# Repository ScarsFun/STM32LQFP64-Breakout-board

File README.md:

# STM32 LQFP64 BREAKOUT BOARD

This is a 64pin STM32 BREAKOUT BOARD inspired by "blue pill" STM32 48pin board (Maple mini clone).
Same features are Improved:

* 3.3v Power supply and VDDA improvements. 
* USB ESD protection.
* added USB reset circuit (not needed for some MCUs).
* Many Cortex M0, M3, M4 STM32 Microcontrolles may be mounted in this PCB layout.
Check notes in schematic and read STM32 datasheets. 
* Eagle PCB, Schematics.

* RTC oscillator is not implemented because no enought PCB spaces to follow STM design guide. ...I'll be pleased if anyone will find a solution 

# CHANGELOG
## 1.3.1 (2021-07-11)
### Fix:
- Fixed reset circuit.
- Silkscreen improvements.

## 1.3 (2020-06-16)
### Features:
- Added support for STM32F401, STM32F410, STM32F411, STM32F412, STM32F413, STM32F423, STM32F446
### Fix:
- Added partitor to VBUS  

## 1.2 (2018-10-11)
### Fix:
- RTC oscillator design dont works. removed from project 

## 1.1 (2018-07-23)
### Features:
- First release lot of bugs

This work is licensed under a [Creative Commons Attribution 4.0 International License.](http://creativecommons.org/licenses/by/4.0/)

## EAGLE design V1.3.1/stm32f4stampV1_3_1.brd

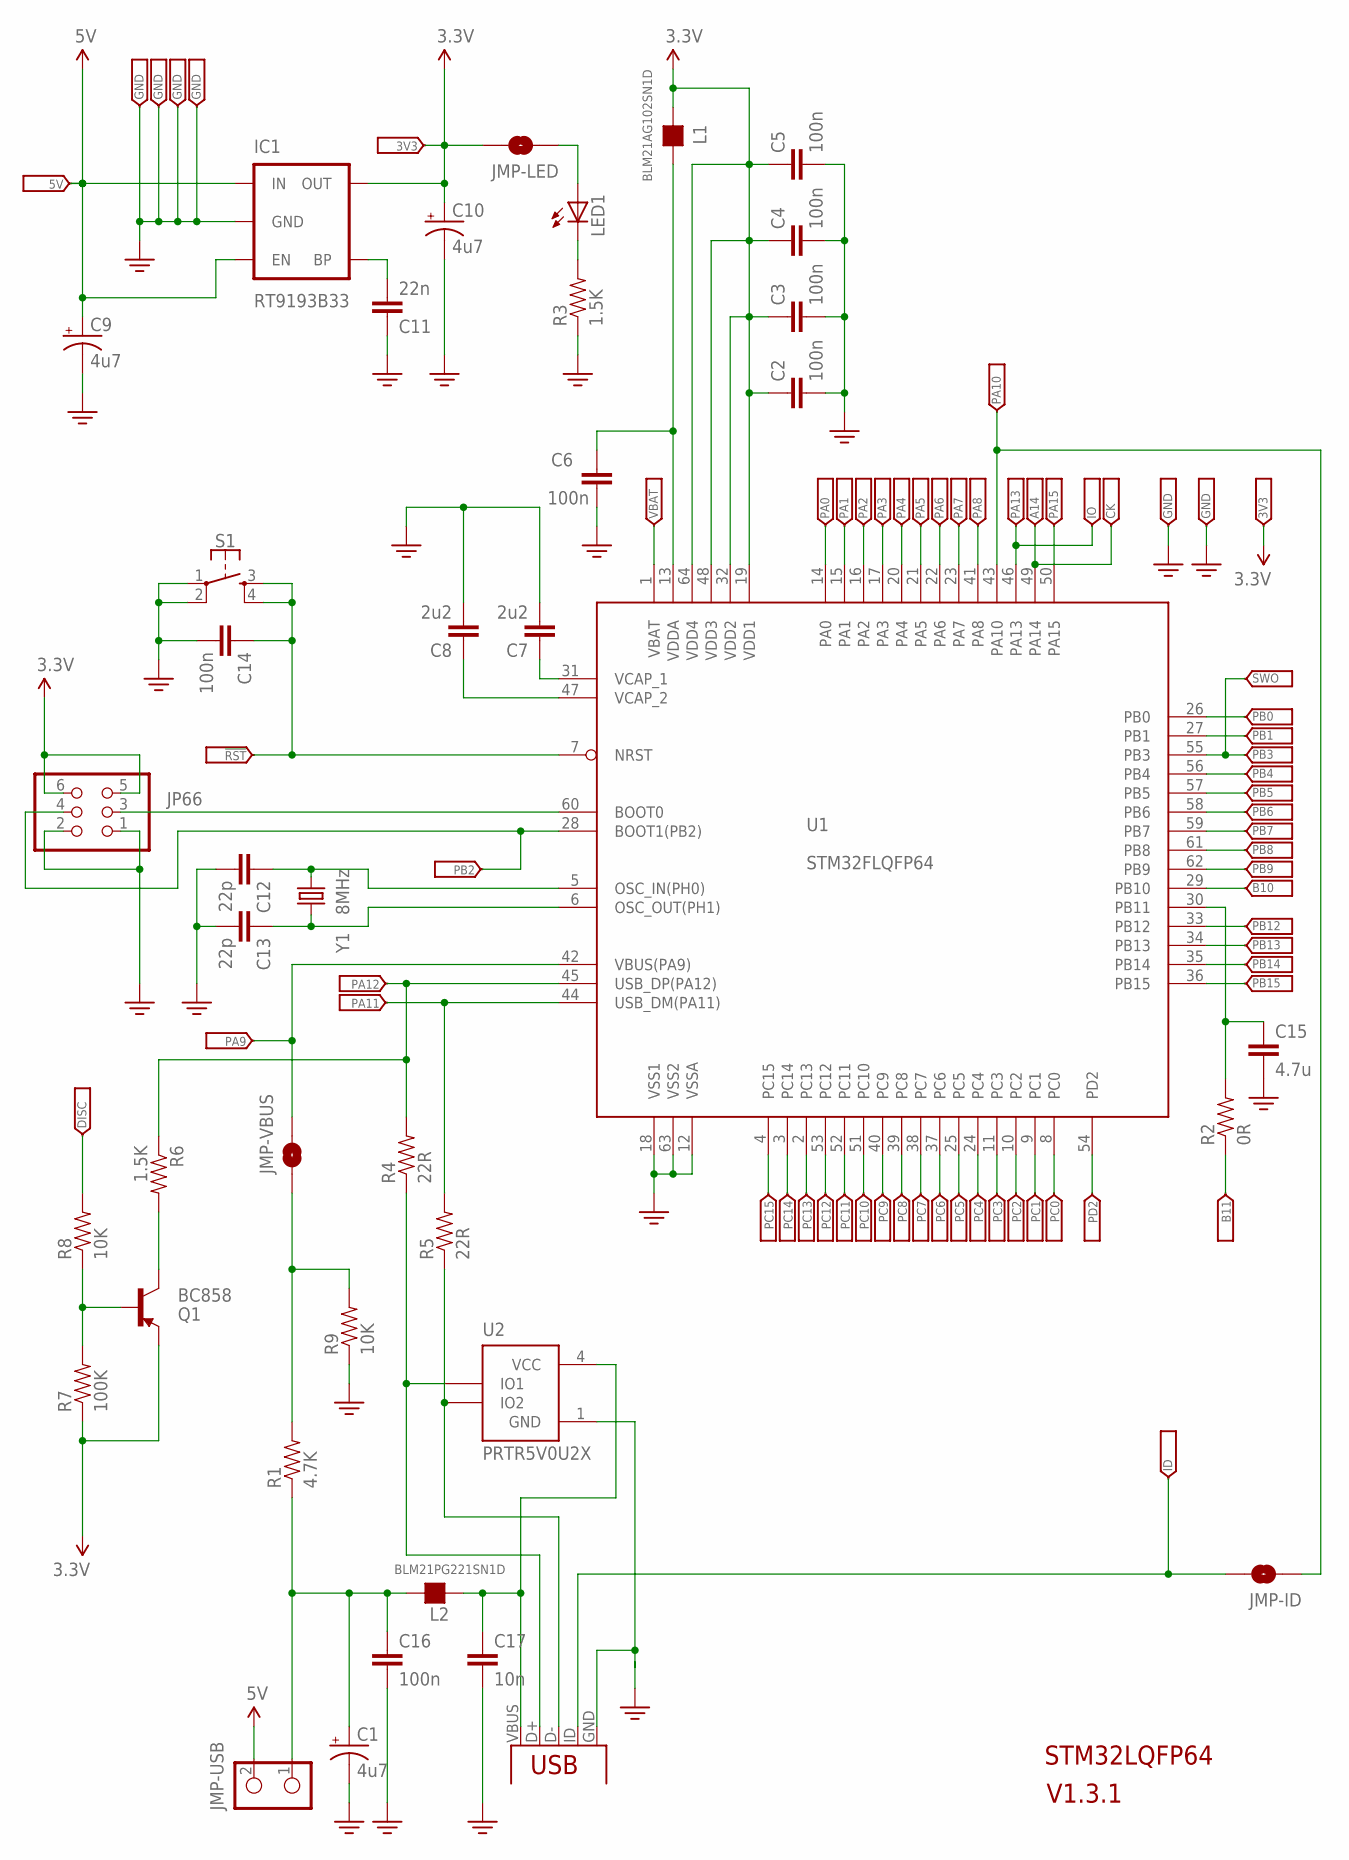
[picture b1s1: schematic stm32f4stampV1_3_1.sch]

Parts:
C1, C9, C10: 4u7; EIA3216-KIT
C2, C3, C4, C5, C6, C14, C16: 100n; 0805
C7, C8: 2u2; 0805
C11: 22n; 0805
C12, C13: 22p; 0805
C15: 4.7u; 0805
C17: 10n; 0805
IC1: RT9193B33; SOT23-5
JMP-ID: SOLDERJUMPERNO; SJ_2S-NO
JMP-LED: SOLDERJUMPERNO; SJ_2S-NO
JMP-USB: JUMPER-2PTH; 1X02
JMP-VBUS: SOLDERJUMPERNO; SJ_2S-NO
JP1: PA12; 1X1-HEADER-HOLE
JP2: 5V; 1X1-HEADER-HOLE
JP3, JP6, JP7, JP55, JP62, JP65: GND; 1X1-HEADER-HOLE
JP4, JP63: 3V3; 1X1-HEADER-HOLE
JP5: DISC; 1X1-HEADER-HOLE
JP8: PB8; 1X1-HEADER-HOLE
JP9: PA10; 1X1-HEADER-HOLE
JP10: PA8; 1X1-HEADER-HOLE
JP11: PA13; 1X1-HEADER-HOLE
JP12: PC9; 1X1-HEADER-HOLE
JP13: PC15; 1X1-HEADER-HOLE
JP14: PC14; 1X1-HEADER-HOLE
JP15: PC13; 1X1-HEADER-HOLE
JP16: PC12; 1X1-HEADER-HOLE
JP17: PC11; 1X1-HEADER-HOLE
JP18: PC10; 1X1-HEADER-HOLE
JP19: PC8; 1X1-HEADER-HOLE
JP20: PC7; 1X1-HEADER-HOLE
JP21: PC6; 1X1-HEADER-HOLE
JP22: PC5; 1X1-HEADER-HOLE
JP23: PC4; 1X1-HEADER-HOLE
JP24: PC3; 1X1-HEADER-HOLE
JP25: PC2; 1X1-HEADER-HOLE
JP26: PC1; 1X1-HEADER-HOLE
JP27: PC0; 1X1-HEADER-HOLE
JP28: PD2; 1X1-HEADER-HOLE
JP29: PA0; 1X1-HEADER-HOLE
JP30: PA1; 1X1-HEADER-HOLE
JP31: PA2; 1X1-HEADER-HOLE
JP32: PA3; 1X1-HEADER-HOLE
JP33: PA4; 1X1-HEADER-HOLE
JP34: PA5; 1X1-HEADER-HOLE
JP35: PA6; 1X1-HEADER-HOLE
JP36: PA7; 1X1-HEADER-HOLE
JP37: A14; 1X1-HEADER-HOLE
JP38: PA15; 1X1-HEADER-HOLE
JP39: PB0; 1X1-HEADER-HOLE
JP40: PB1; 1X1-HEADER-HOLE
JP41: PB3; 1X1-HEADER-HOLE
JP42: PB4; 1X1-HEADER-HOLE
JP43: PB5; 1X1-HEADER-HOLE
JP44: PB6; 1X1-HEADER-HOLE
JP45: PB7; 1X1-HEADER-HOLE
JP46: PB9; 1X1-HEADER-HOLE
JP47: B10; 1X1-HEADER-HOLE
JP48: B11; 1X1-HEADER-HOLE
JP49: PB12; 1X1-HEADER-HOLE
JP50: PB13; 1X1-HEADER-HOLE
JP51: PB14; 1X1-HEADER-HOLE
JP52: PB15; 1X1-HEADER-HOLE
JP53: VBAT; 1X1-HEADER-HOLE
JP54: !RST; 1X1-HEADER-HOLE
JP56: ID; 1X1-HEADER-HOLE
JP57: PB2; 1X1-HEADER-HOLE
JP58: PA11; 1X1-HEADER-HOLE
JP59: IO; 1X1-HEADER-HOLE
JP60: CK; 1X1-HEADER-HOLE
JP61: SWO; 1X1-HEADER-HOLE
JP64: PA9; 1X1-HEADER-HOLE
JP66: PINHD-2X3; 2X03
L1: BLM21AG102SN1D; L0805
L2: BLM21PG221SN1D; L0805
LED1: LEDSML0805; SML0805
Q1: BC858; SOT23-3
R1: 4.7K; 0805
R2: 0R; 0805
R3, R6: 1.5K; 0805
R4, R5: 22R; 0805
R7: 100K; 0805
R8, R9: 10K; 0805
S1: MOMENTARY-SWITCH-SPST-2-SMD-5.2MM; TACTILE_SWITCH_SMD_5.2MM
U1: STM32FLQFP64; LQFP64
U2: PRTR5V0U2X; SOT-143B
USB: USB-MICROB-SMD
Y1: 8MHz; CRYSTAL-SMD-5X3

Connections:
3.3V: C2.1, C3.1, C4.1, C5.1, C10.A (+), IC1.5 (OUT), JMP-LED.2, JP4.1, JP63.1, JP66.5, JP66.6, L1.2, Q1.2 (E), R7.1, U1.19 (VDD1), U1.32 (VDD2), U1.48 (VDD3), U1.64 (VDD4)
5V: C9.A (+), IC1.1 (IN), IC1.3 (EN), JMP-USB.2, JP2.1
GND: C1.C (-), C2.2, C3.2, C4.2, C5.2, C6.2, C7.2, C8.2, C9.C (-), C10.C (-), C11.1, C12.2, C13.2, C14.2, C15.2, C16.2, C17.2, IC1.2 (GND), JP3.1, JP6.1, JP7.1, JP55.1, JP62.1, JP65.1, JP66.1, JP66.2, R3.1, R9.1, S1.1, S1.2, U1.12 (VSSA), U1.18 (VSS1), U1.63 (VSS2), U2.1 (GND), USB.GND, USB.MT1, USB.MT2, USB.MT3, USB.MT4
unnamed: JP1.1, R4.2, R6.1, U1.45 (USB_DP(PA12))
unnamed: JP13.1, U1.4 (PC15)
unnamed: C1.A (+), C16.1, JMP-USB.1, L2.2, R1.1
unnamed: JP12.1, U1.40 (PC9)
unnamed: C17.1, L2.1, U2.4 (VCC), USB.VBUS
unnamed: JP58.1, R5.2, U1.44 (USB_DM(PA11))
unnamed: JP8.1, U1.61 (PB8)
unnamed: C11.2, IC1.4 (BP)
unnamed: JP66.3, U1.60 (BOOT0)
unnamed: JP10.1, U1.41 (PA8)
unnamed: JP11.1, JP59.1, U1.46 (PA13)
unnamed: C13.1, U1.6 (OSC_OUT(PH1)), Y1.1
unnamed: C7.1, U1.31 (VCAP_1)
unnamed: C8.1, U1.47 (VCAP_2)
unnamed: C12.1, U1.5 (OSC_IN(PH0)), Y1.3 (2)
unnamed: JP57.1, JP66.4, U1.28 (BOOT1(PB2))
unnamed: C14.1, JP54.1, S1.3, S1.4, U1.7 (NRST)
unnamed: LED1.C, R3.2
unnamed: C6.1, L1.1, U1.13 (VDDA)
unnamed: JMP-ID.2, JP56.1, USB.ID
unnamed: R5.1, U2.3 (IO2), USB.D-
unnamed: JMP-ID.1, JP9.1, U1.43 (PA10)
unnamed: JP14.1, U1.3 (PC14)
unnamed: JMP-VBUS.1, R1.2, R9.2
unnamed: JP15.1, U1.2 (PC13)
unnamed: JP16.1, U1.53 (PC12)
unnamed: JP17.1, U1.52 (PC11)
unnamed: JP18.1, U1.51 (PC10)
unnamed: JP19.1, U1.39 (PC8)
unnamed: JP20.1, U1.38 (PC7)
unnamed: JP21.1, U1.37 (PC6)
unnamed: JP22.1, U1.25 (PC5)
unnamed: JP23.1, U1.24 (PC4)
unnamed: JP24.1, U1.11 (PC3)
unnamed: JP25.1, U1.10 (PC2)
unnamed: JP26.1, U1.9 (PC1)
unnamed: JP27.1, U1.8 (PC0)
unnamed: JP28.1, U1.54 (PD2)
unnamed: JP29.1, U1.14 (PA0)
unnamed: JP30.1, U1.15 (PA1)
unnamed: JP31.1, U1.16 (PA2)
unnamed: JP32.1, U1.17 (PA3)
unnamed: JP33.1, U1.20 (PA4)
unnamed: JP34.1, U1.21 (PA5)
unnamed: JP35.1, U1.22 (PA6)
unnamed: JP36.1, U1.23 (PA7)
unnamed: JP37.1, JP60.1, U1.49 (PA14)
unnamed: JP38.1, U1.50 (PA15)
unnamed: JP39.1, U1.26 (PB0)
unnamed: JP40.1, U1.27 (PB1)
unnamed: JP41.1, JP61.1, U1.55 (PB3)
unnamed: JP42.1, U1.56 (PB4)
unnamed: JP43.1, U1.57 (PB5)
unnamed: JP44.1, U1.58 (PB6)
unnamed: JP45.1, U1.59 (PB7)
unnamed: JP46.1, U1.62 (PB9)
unnamed: JP47.1, U1.29 (PB10)
unnamed: C15.1, R2.2, U1.30 (PB11)
unnamed: JP49.1, U1.33 (PB12)
unnamed: JP50.1, U1.34 (PB13)
unnamed: JP51.1, U1.35 (PB14)
unnamed: JP52.1, U1.36 (PB15)
unnamed: JP53.1, U1.1 (VBAT)
unnamed: R4.1, U2.2 (IO1), USB.D+
unnamed: JMP-LED.1, LED1.A
unnamed: JMP-VBUS.2, JP64.1, U1.42 (VBUS(PA9))
unnamed: Q1.3 (C), R6.2
unnamed: JP48.1, R2.1
unnamed: Q1.1 (B), R7.2, R8.1
unnamed: JP5.1, R8.2

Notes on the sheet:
STM32LQFP64
V1.3.1

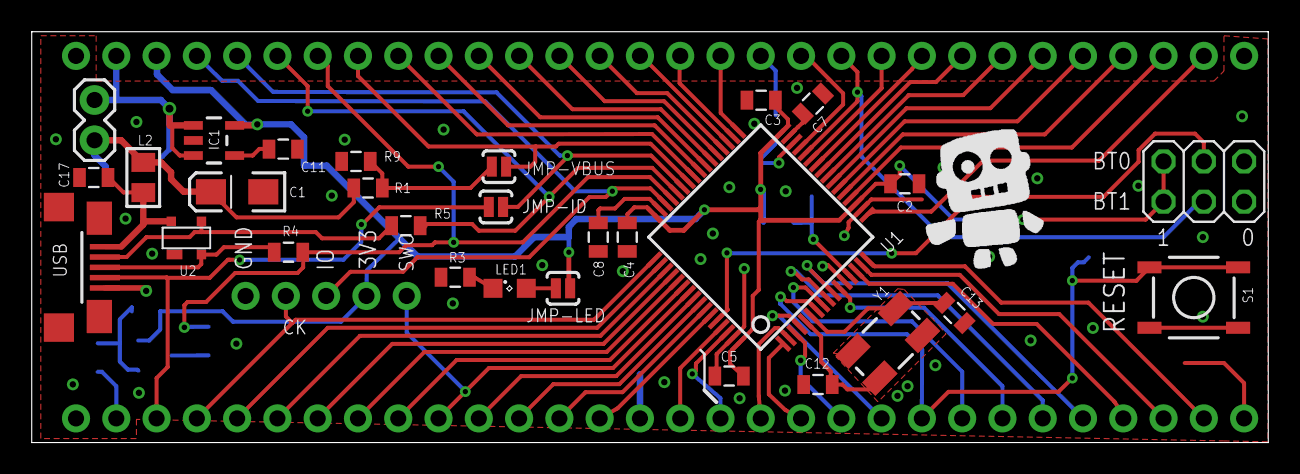
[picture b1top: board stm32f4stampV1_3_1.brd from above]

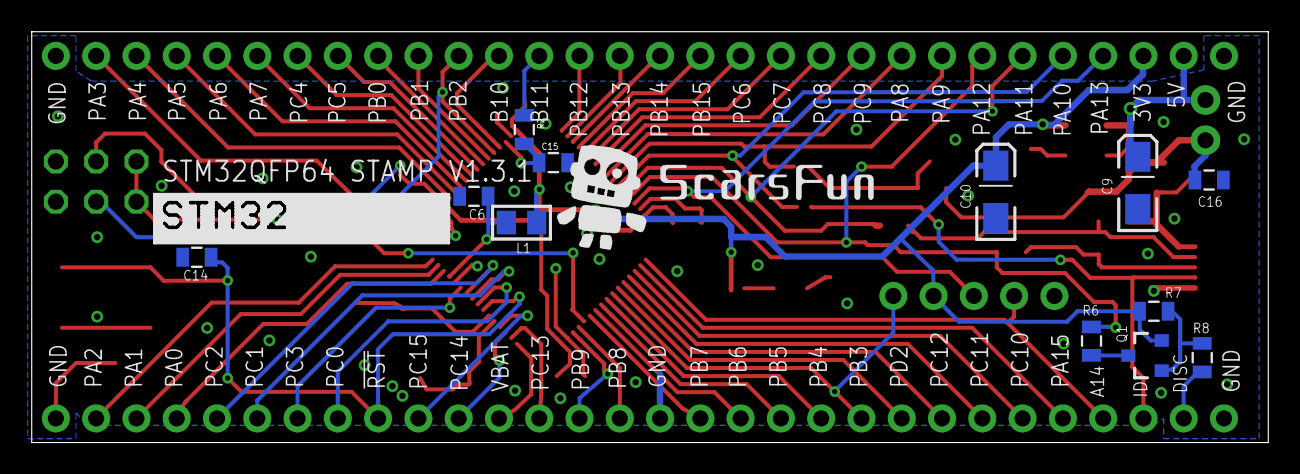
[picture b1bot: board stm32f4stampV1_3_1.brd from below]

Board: 2 copper layers, 78.0 x 25.9 mm, 106 parts (12 on the bottom side), 73 nets.

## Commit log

2020-06-16 V1.3 released
2021-07-11 V1.3.1 update

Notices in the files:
parts and their libraries:
rc-master: Copyright (C) 2007, Bob Starr
SparkFun-Switches: Licensing: Creative Commons ShareAlike 4.0 International - https://creativecommons.org/licenses/by-sa/4.0
SparkFun: Licensing: CC v3.0 Share-Alike You are welcome to use this library for commercial purposes.
